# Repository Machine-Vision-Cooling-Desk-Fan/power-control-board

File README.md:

Using KiCAD 10.0.7

Open Schematic Preview: https://kicanvas.org/?repo=https%3A%2F%2Fgithub.com%2FMachine-Vision-Cooling-Desk-Fan%2Fpower-control-board

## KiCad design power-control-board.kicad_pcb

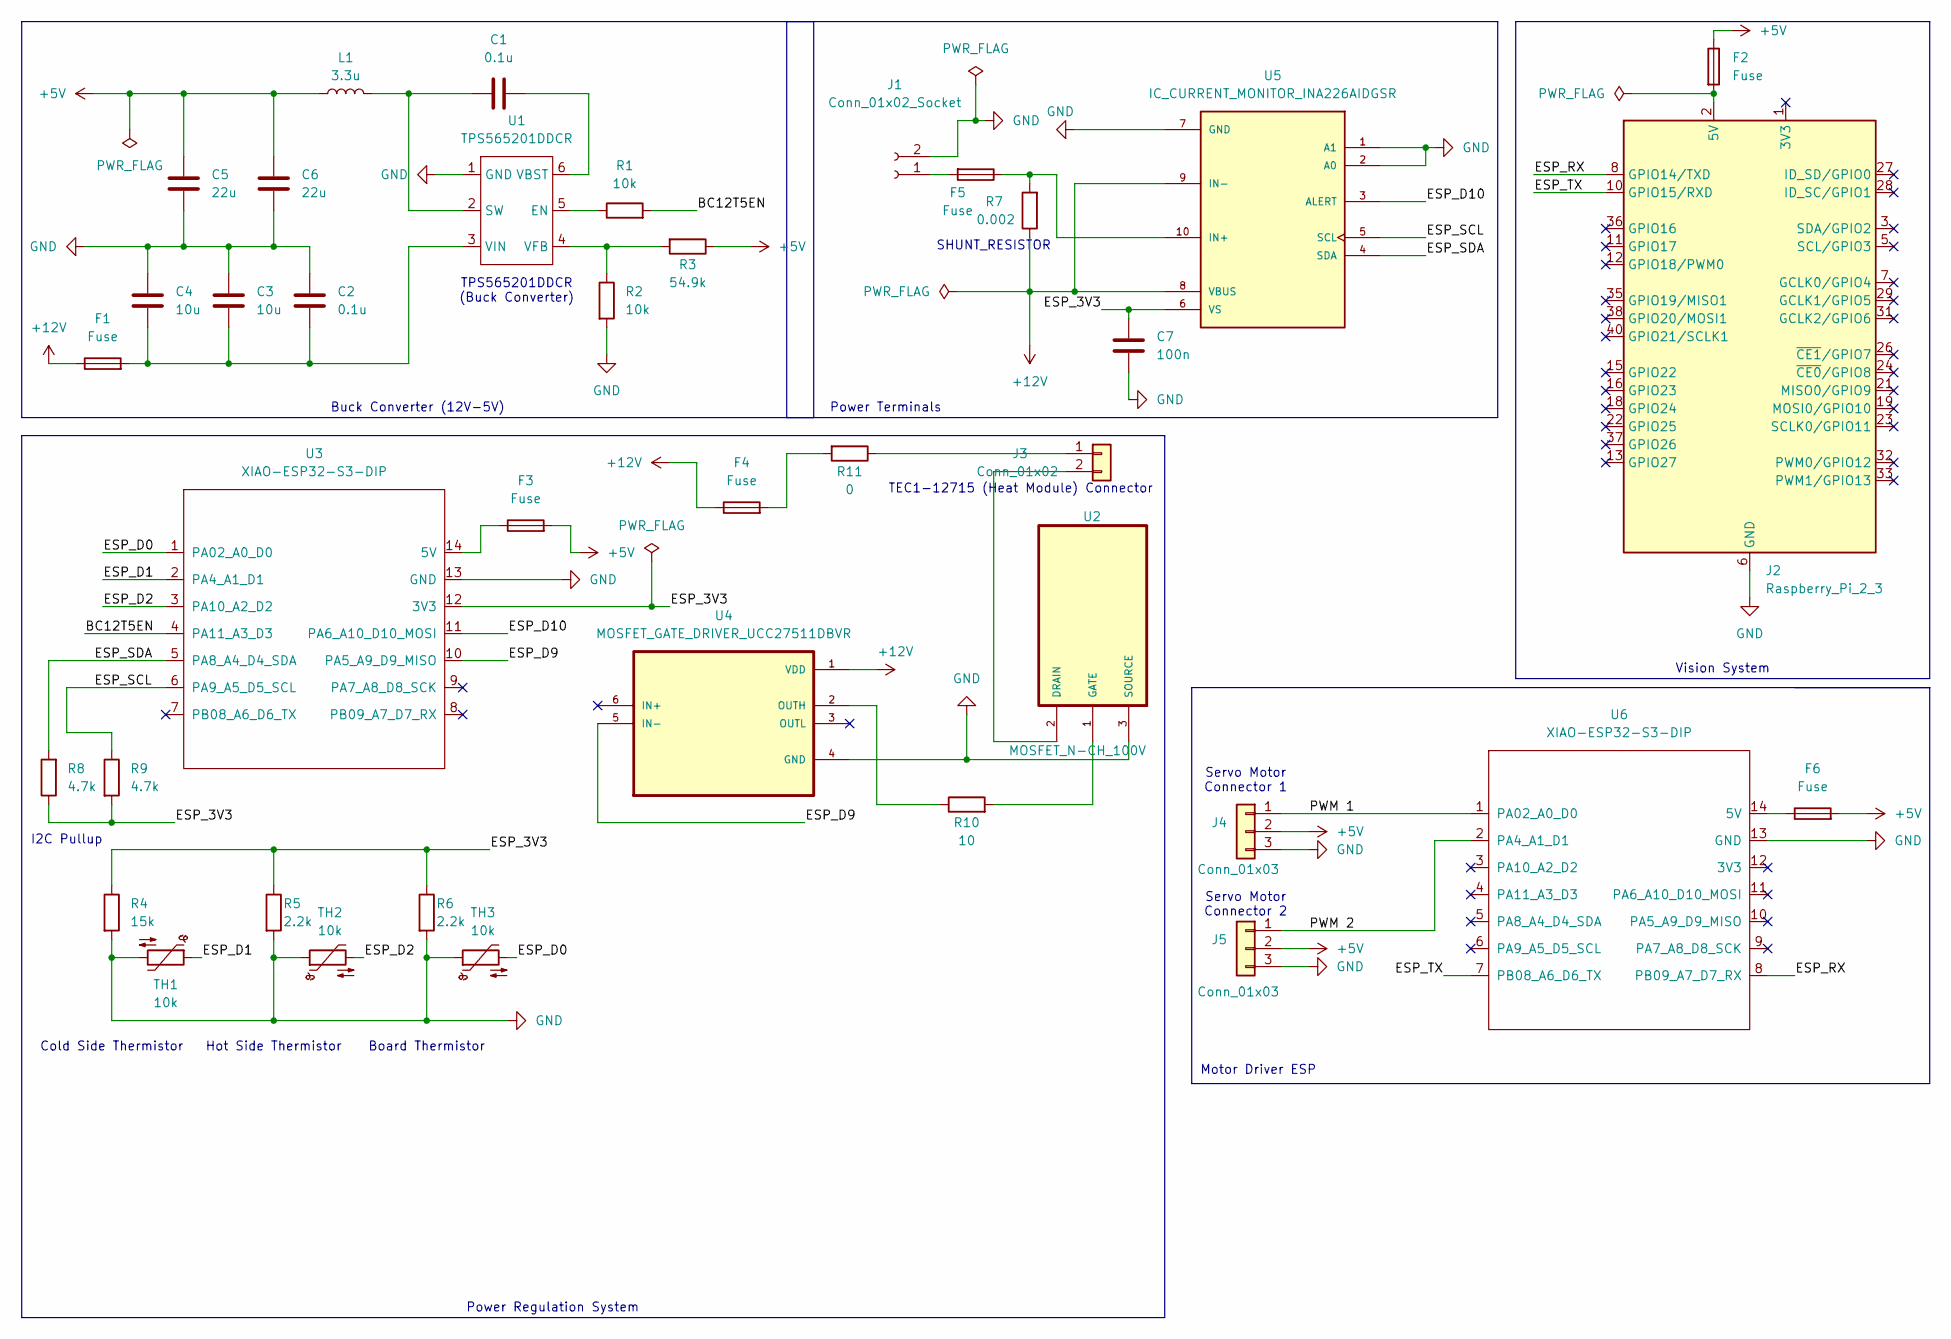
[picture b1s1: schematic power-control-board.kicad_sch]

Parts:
C1, C2: 0.1u; C_0603_1608Metric
C3, C4: 10u; C_1210_3225Metric
C5, C6: 22u; C_1206_3216Metric
C7: 100n; C_1206_3216Metric_Pad1.33x1.80mm_HandSolder
F1, F2, F3, F4, F5, F6: Fuse; Fuseholder_Blade_Mini_Keystone_3568
J1: Conn_01x02_Socket; Amphenol_Anytek_VC0200510000G
J2: Raspberry_Pi_2_3; PinSocket_2x20_P2.54mm_Vertical
J3: Conn_01x02; Screw_Terminal_Phoenix_Contact_1935776
J4, J5: Conn_01x03; PinHeader_1x03_P2.54mm_Vertical
L1: 3.3u; L_Bourns_SRP7028A_7.3x6.6mm
R1, R2: 10k; R_0201_0603Metric
R3: 54.9k; R_0201_0603Metric
R4: 15k; R_1206_3216Metric_Pad1.30x1.75mm_HandSolder
R5: 2.2k; R_1206_3216Metric_Pad1.30x1.75mm_HandSolder
R6: 2.2k; LED_1206_3216Metric_Pad1.42x1.75mm_HandSolder
R7: 0.002; R_2512_6332Metric
R8, R9: 4.7k; R_1206_3216Metric_Pad1.30x1.75mm_HandSolder
R10: 10; R_1206_3216Metric_Pad1.30x1.75mm_HandSolder
R11: 0; R_2512_6332Metric_Pad1.40x3.35mm_HandSolder
TH1, TH2, TH3: 10k; PinHeader_1x02_P2.54mm_Vertical
U1: TPS565201DDCR; Buck_Converter_TPS565201DDCR_SOT95P280X110-6N
U2: MOSFET_N-CH_100V; MOSFET_N-CH_100V_200A_DDPAK_CSD19536KTT
U3, U6: XIAO-ESP32-S3-DIP
U4: MOSFET_GATE_DRIVER_UCC27511DBVR; DigiKey_Part_Number 296-30285-1-ND
U5: IC_CURRENT_MONITOR_INA226AIDGSR; PARTREV B; DigiKey_Part_Number 296-29034-1-ND

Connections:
+5V: C5.1, C6.1, F2.1, F3.2, F6.2, J4.2, J5.2, L1.1, R3.1
+12V: F1.1, F4.1, R7.1, U4.1 (VDD), U5.8 (VBUS), U5.9 (IN-)
/BC12T5EN: R1.2, U3.4 (PA11_A3_D3)
/ESP_3V3: C7.2, R4.1, R5.1, R6.1, R8.1, R9.2, U3.12 (3V3), U5.6 (VS)
/ESP_D0: TH3.2, U3.1 (PA02_A0_D0)
/ESP_D1: TH1.1, U3.2 (PA4_A1_D1)
/ESP_D2: TH2.2, U3.3 (PA10_A2_D2)
/ESP_D9: U3.10 (PA5_A9_D9_MISO), U4.5 (IN-)
/ESP_D10: U3.11 (PA6_A10_D10_MOSI), U5.3 (ALERT)
/ESP_RX: J2.8 (GPIO14/TXD), U6.8 (PB09_A7_D7_RX)
/ESP_SCL: R9.1, U3.6 (PA9_A5_D5_SCL), U5.5 (SCL)
/ESP_SDA: R8.2, U3.5 (PA8_A4_D4_SDA), U5.4 (SDA)
/ESP_TX: J2.10 (GPIO15/RXD), U6.7 (PB08_A6_D6_TX)
/PWM 1: J4.1, U6.1 (PA02_A0_D0)
/PWM 2: J5.1, U6.2 (PA4_A1_D1)
GND: C2.1, C3.1, C4.1, C5.2, C6.2, C7.1, J1.2, J2.6 (GND), J2.9 (GND), J2.14 (GND), J2.20 (GND), J2.25 (GND), J2.30 (GND), J2.34 (GND), J2.39 (GND), J4.3, J5.3, R2.2, R4.2, R5.2, R6.2, TH1.2, TH2.1, TH3.1, U1.1 (GND), U2.3 (SOURCE), U3.13 (GND), U4.4 (GND), U5.1 (A1), U5.2 (A0), U5.7 (GND), U6.13 (GND)
unnamed: F2.2, J2.2 (5V), J2.4 (5V)
unnamed: F4.2, R11.2
unnamed: F5.2, J1.1
unnamed: J3.1, R11.1
unnamed: J3.2, U2.2 (DRAIN)
unnamed: R1.1, U1.5 (EN)
unnamed: C1.1, L1.2, U1.2 (SW)
unnamed: C1.2, U1.6 (VBST)
unnamed: R2.1, R3.2, U1.4 (VFB)
unnamed: C2.2, C3.2, C4.2, F1.2, U1.3 (VIN)
unnamed: R10.2, U2.1 (GATE)
unnamed: F3.1, U3.14 (5V)
unnamed: R10.1, U4.2 (OUTH)
unnamed: F5.1, R7.2, U5.10 (IN+)
unnamed: F6.1, U6.14 (5V)

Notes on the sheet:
TPS565201DDCR (Buck Converter)
Motor Driver ESP
Vision System
TEC1-12715 (Heat Module) Connector
Servo Motor Connector 1
Power Terminals
Board Thermistor
I2C Pullup
Power Regulation System
SHUNT_RESISTOR
Hot Side Thermistor
Buck Converter (12V-5V)
Servo Motor Connector 2
Cold Side Thermistor

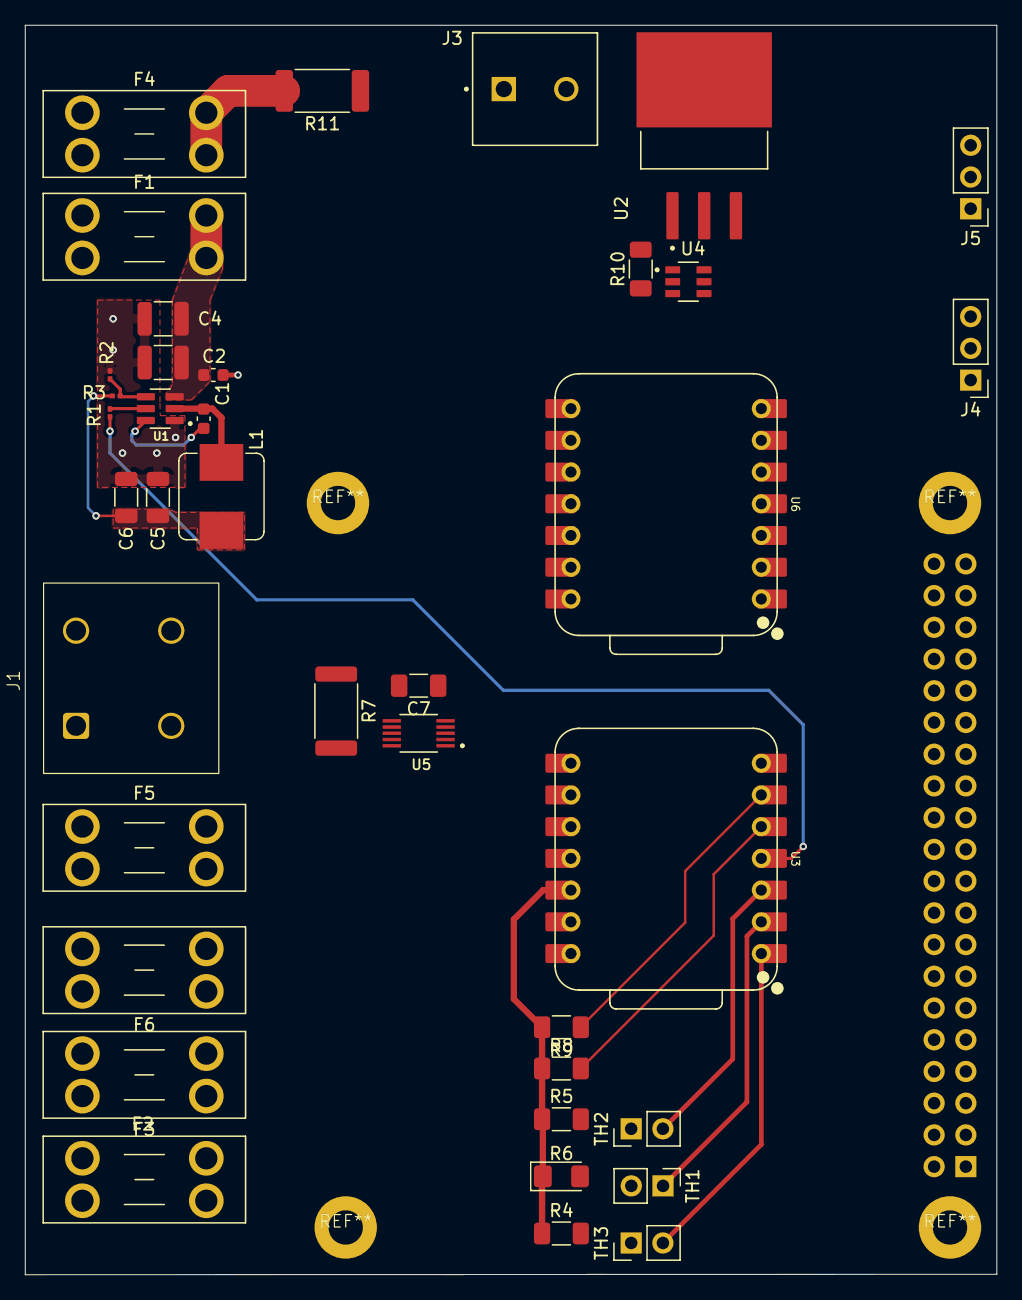
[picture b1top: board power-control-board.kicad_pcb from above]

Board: 4 copper layers, 77.8 x 100.0 mm, 39 parts (1 on the bottom side), 31 nets.
